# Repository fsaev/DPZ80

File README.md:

# DPZ80
Homebrew Z80 Development Platform

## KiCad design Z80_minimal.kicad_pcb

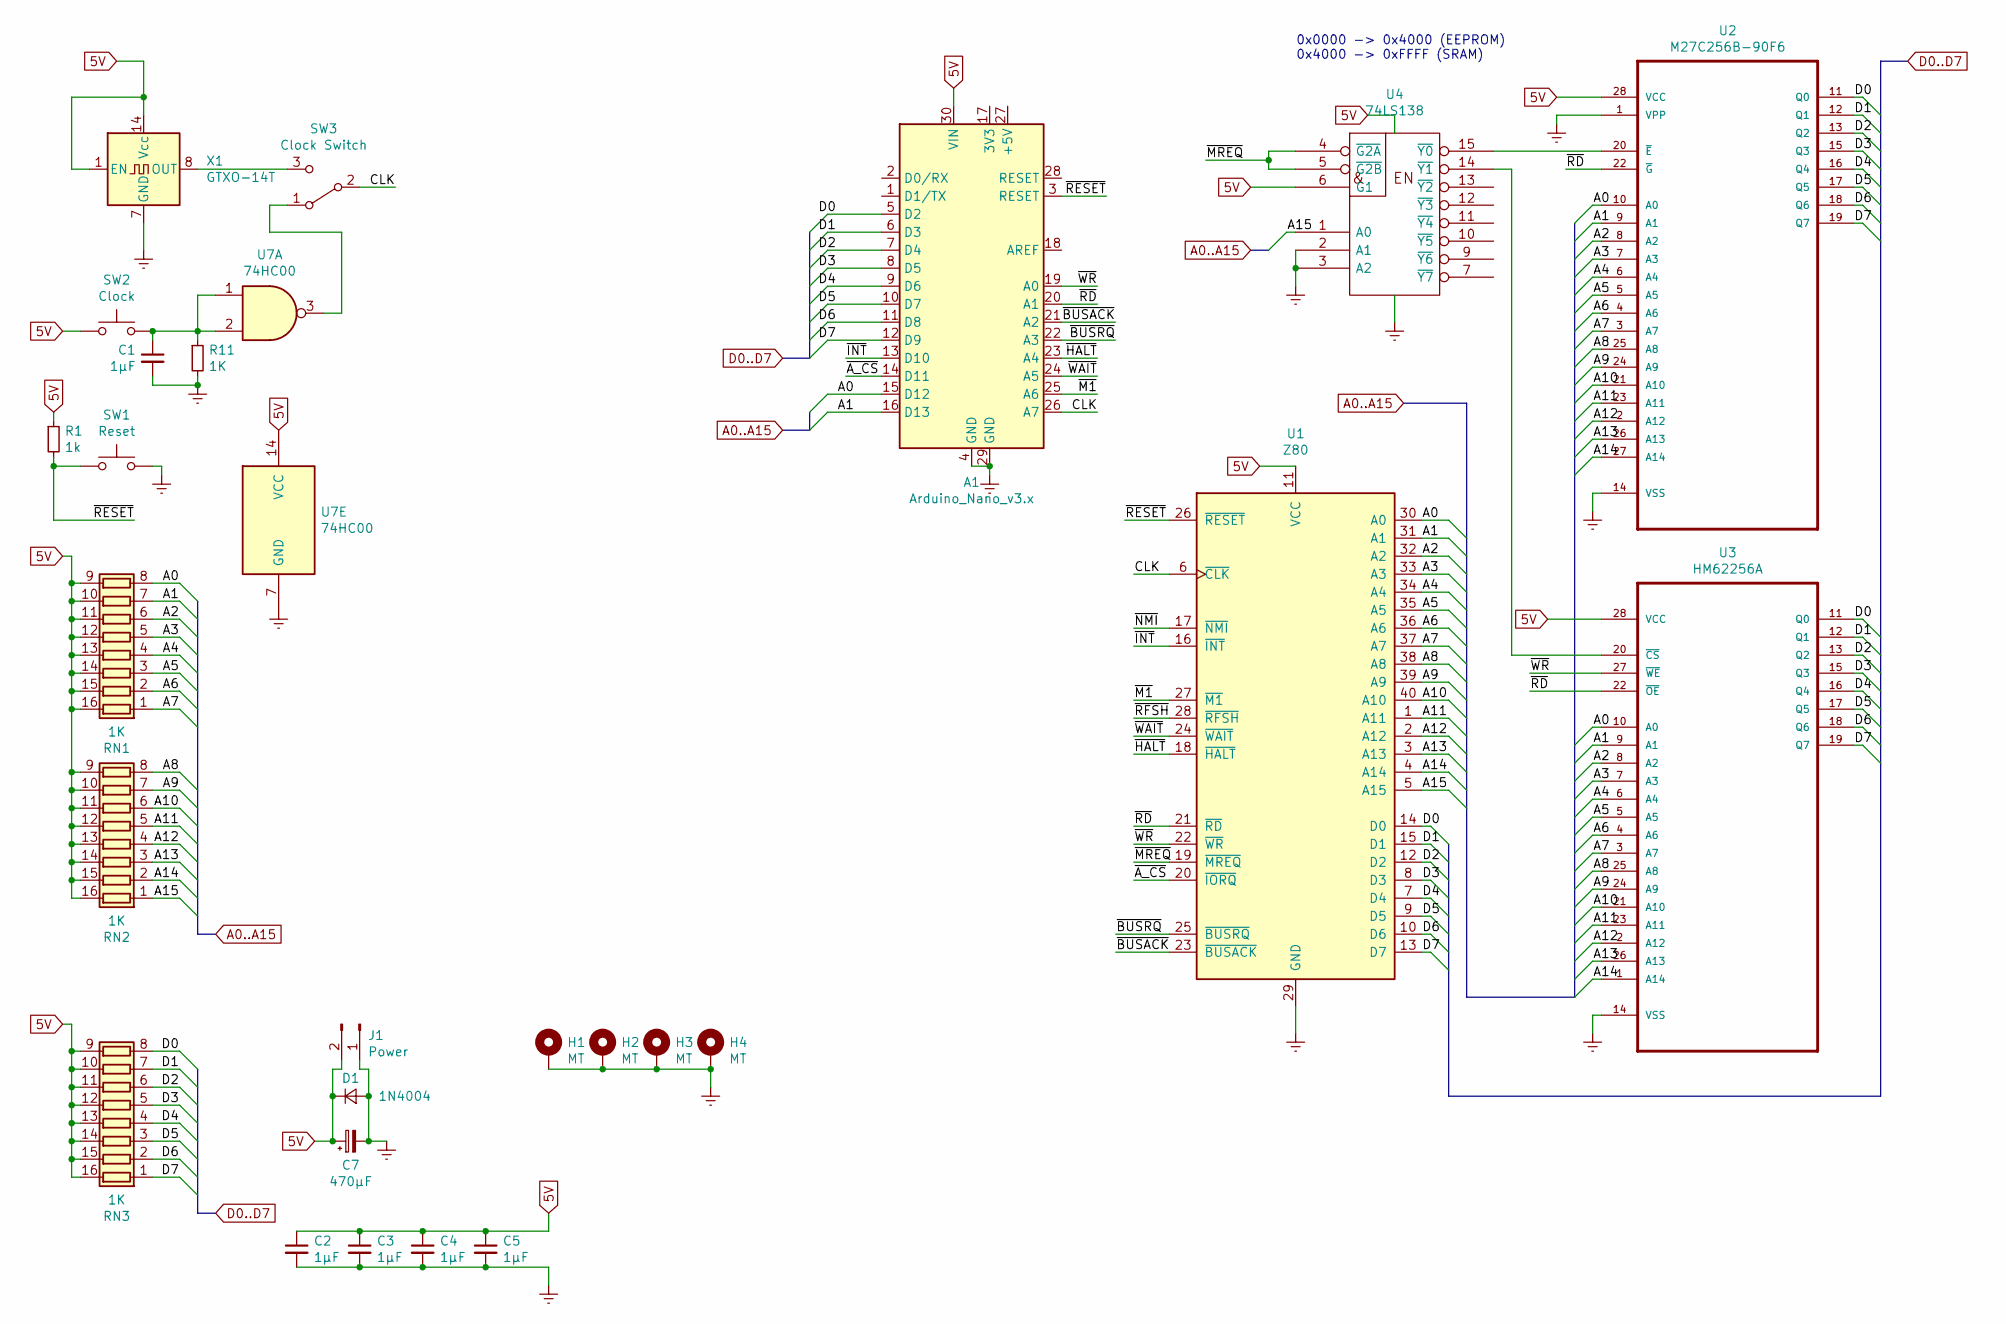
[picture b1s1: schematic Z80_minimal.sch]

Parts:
A1: Arduino_Nano_v3.x; Arduino_Nano
C1, C2, C3, C4, C5: 1µF; C_Rect_L9.0mm_W2.7mm_P7.50mm_MKT
C7: 470µF; CP_Radial_D10.0mm_P5.00mm
D1: 1N4004; D_DO-41_SOD81_P10.16mm_Horizontal
H1, H2, H3, H4: MT; MountingHole_2.2mm_M2_Pad
J1: Power; PinHeader_1x02_P2.00mm_Vertical
R1: 1k; R_Axial_DIN0207_L6.3mm_D2.5mm_P10.16mm_Horizontal
R11: 1K; R_Axial_DIN0207_L6.3mm_D2.5mm_P10.16mm_Horizontal
RN1, RN2, RN3: 1K; DIP-16_W7.62mm
SW1: Reset; SW_PUSH_6mm
SW2: Clock; SW_PUSH_6mm
SW3: Clock Switch; SW_Slide_1P2T_CK_OS102011MS2Q
U1: Z80; DIP-40_W15.24mm
U2: M27C256B-90F6; DIP-28_W15.24mm
U3: HM62256A; DIP-28_W15.24mm
U4: 74LS138; DIP-16_W7.62mm
U7: 74HC00; DIP-14_W7.62mm
X1: GTXO-14T; Oscillator_DIP-14

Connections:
5V: A1.30 (VIN), C2.1, C3.1, C4.1, C5.1, C7.1, D1.1 (K), J1.2, R1.1, RN1.9 (R8.2), RN1.10 (R7.2), RN1.11 (R6.2), RN1.12 (R5.2), RN1.13 (R4.2), RN1.14 (R3.2), RN1.15 (R2.2), RN1.16 (R1.2), RN2.9 (R8.2), RN2.10 (R7.2), RN2.11 (R6.2), RN2.12 (R5.2), RN2.13 (R4.2), RN2.14 (R3.2), RN2.15 (R2.2), RN2.16 (R1.2), RN3.9 (R8.2), RN3.10 (R7.2), RN3.11 (R6.2), RN3.12 (R5.2), RN3.13 (R4.2), RN3.14 (R3.2), RN3.15 (R2.2), RN3.16 (R1.2), SW2.1, U1.11 (VCC), U2.28 (VCC), U3.28 (VCC), U4.6 (G1), U4.16 (VCC), U7.14 (VCC), X1.1 (EN), X1.14 (Vcc)
/A0: A1.15 (D12), RN1.8 (R8.1), U1.30 (A0), U2.10 (A0), U3.10 (A0)
/A1: A1.16 (D13), RN1.7 (R7.1), U1.31 (A1), U2.9 (A1), U3.9 (A1)
/A2: RN1.6 (R6.1), U1.32 (A2), U2.8 (A2), U3.8 (A2)
/A3: RN1.5 (R5.1), U1.33 (A3), U2.7 (A3), U3.7 (A3)
/A4: RN1.4 (R4.1), U1.34 (A4), U2.6 (A4), U3.6 (A4)
/A5: RN1.3 (R3.1), U1.35 (A5), U2.5 (A5), U3.5 (A5)
/A6: RN1.2 (R2.1), U1.36 (A6), U2.4 (A6), U3.4 (A6)
/A7: RN1.1 (R1.1), U1.37 (A7), U2.3 (A7), U3.3 (A7)
/A8: RN2.8 (R8.1), U1.38 (A8), U2.25 (A8), U3.25 (A8)
/A9: RN2.7 (R7.1), U1.39 (A9), U2.24 (A9), U3.24 (A9)
/A10: RN2.6 (R6.1), U1.40 (A10), U2.21 (A10), U3.21 (A10)
/A11: RN2.5 (R5.1), U1.1 (A11), U2.23 (A11), U3.23 (A11)
/A12: RN2.4 (R4.1), U1.2 (A12), U2.2 (A12), U3.2 (A12)
/A13: RN2.3 (R3.1), U1.3 (A13), U2.26 (A13), U3.26 (A13)
/A14: RN2.2 (R2.1), U1.4 (A14), U2.27 (A14), U3.1 (A14)
/A15: RN2.1 (R1.1), U1.5 (A15), U4.1 (A0)
/CLK: A1.26 (A7), SW3.2 (B), U1.6 (~CLK~)
/D0: A1.5 (D2), RN3.8 (R8.1), U1.14 (D0), U2.11 (Q0), U3.11 (Q0)
/D1: A1.6 (D3), RN3.7 (R7.1), U1.15 (D1), U2.12 (Q1), U3.12 (Q1)
/D2: A1.7 (D4), RN3.6 (R6.1), U1.12 (D2), U2.13 (Q2), U3.13 (Q2)
/D3: A1.8 (D5), RN3.5 (R5.1), U1.8 (D3), U2.15 (Q3), U3.15 (Q3)
/D4: A1.9 (D6), RN3.4 (R4.1), U1.7 (D4), U2.16 (Q4), U3.16 (Q4)
/D5: A1.10 (D7), RN3.3 (R3.1), U1.9 (D5), U2.17 (Q5), U3.17 (Q5)
/D6: A1.11 (D8), RN3.2 (R2.1), U1.10 (D6), U2.18 (Q6), U3.18 (Q6)
/D7: A1.12 (D9), RN3.1 (R1.1), U1.13 (D7), U2.19 (Q7), U3.19 (Q7)
/~A_CS: A1.14 (D11), U1.20 (~IORQ~)
/~BUSACK: A1.21 (A2), U1.23 (~BUSACK~)
/~BUSRQ: A1.22 (A3), U1.25 (~BUSRQ~)
/~HALT: A1.23 (A4), U1.18 (~HALT~)
/~INT: A1.13 (D10), U1.16 (~INT~)
/~M1: A1.25 (A6), U1.27 (~M1~)
/~MREQ: U1.19 (~MREQ~), U4.4 (~G2A), U4.5 (~G2B)
/~NMI: U1.17 (~NMI~)
/~RD: A1.20 (A1), U1.21 (~RD~), U2.22 (~G), U3.22 (~OE)
/~RESET: A1.3 (RESET), R1.2, SW1.1, U1.26 (~RESET~)
/~RFSH: U1.28 (~RFSH~)
/~WAIT: A1.24 (A5), U1.24 (~WAIT~)
/~WR: A1.19 (A0), U1.22 (~WR~), U3.27 (~WE)
Earth: A1.4 (GND), A1.29 (GND), C1.2, C2.2, C3.2, C4.2, C5.2, C7.2, D1.2 (A), H1.1, H2.1, H3.1, H4.1, J1.1, R11.2, SW1.2, U1.29 (GND), U2.1 (VPP), U2.14 (VSS), U3.14 (VSS), U4.2 (A1), U4.3 (A2), U4.8 (GND), U7.7 (GND), X1.7 (GND)
unnamed: C1.1, R11.1, SW2.2, U7.1, U7.2
unnamed: SW3.1 (A), U7.3
unnamed: SW3.3 (C), X1.8 (OUT)
unnamed: U2.20 (~E), U4.15 (~Y0)
unnamed: U3.20 (~CS), U4.14 (~Y1)

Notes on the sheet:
0x0000 -> 0x4000 (EEPROM) 0x4000 -> 0xFFFF (SRAM)

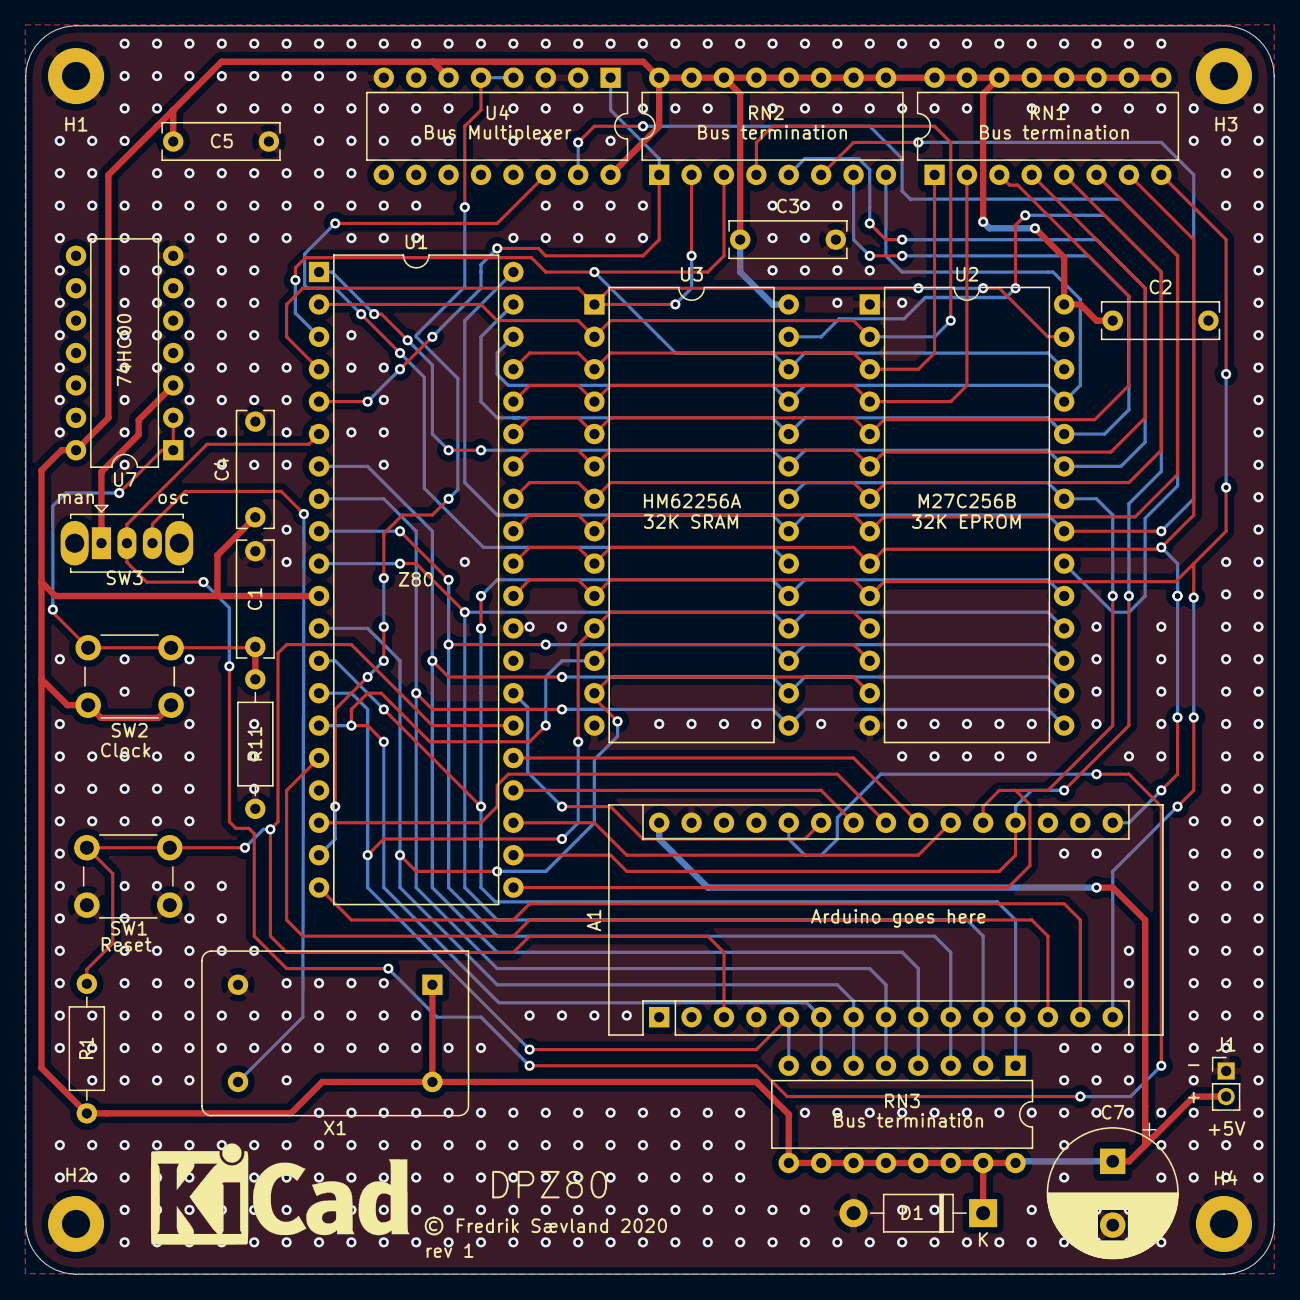
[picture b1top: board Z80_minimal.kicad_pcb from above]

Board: 2 copper layers, 97.9 x 97.9 mm, 27 parts (0 on the bottom side), 43 nets.

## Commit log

2020-03-10 Add inital project data
2020-03-10 Add image of board

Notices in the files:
Z80_minimal.kicad_pcb:
© Fredrik Sævland 2020
